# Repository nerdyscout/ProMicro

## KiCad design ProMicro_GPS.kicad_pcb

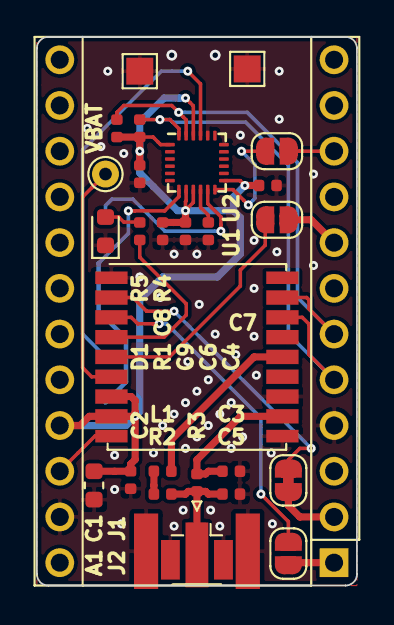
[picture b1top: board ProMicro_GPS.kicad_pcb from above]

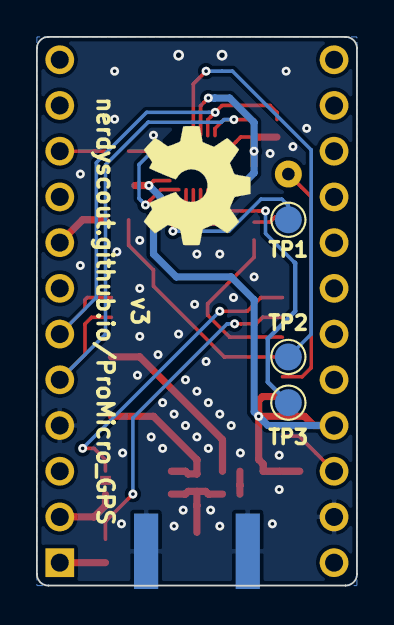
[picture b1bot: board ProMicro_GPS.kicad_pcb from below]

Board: 2 copper layers, 17.8 x 30.5 mm, 32 parts (4 on the bottom side), 24 nets.

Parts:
A1: Sparkfun_Pro_Micro_3V3; Sparkfun_Pro_Micro
C1: 4,7µ; C_0603_1608Metric
C2, C4, C7, C8, C9: 100n; C_0402_1005Metric
C3, C5: DNP; C_0402_1005Metric
C6: 10n; C_0402_1005Metric
D1: LED; LED_0603_1608Metric
J1: uFL; U.FL_Hirose_U.FL-R-SMT-1_Vertical
J2: Coax; SMA_Samtec_SMA-J-P-H-ST-EM1_EdgeMount
JP1: Jumper_NC_Small; SolderJumper-2_P1.3mm_Bridged_RoundedPad1.0x1.5mm
JP2: Jumper_NO_Small; SolderJumper-2_P1.3mm_Open_RoundedPad1.0x1.5mm
JP3, JP4: SolderJumper_2_Open; SolderJumper-2_P1.3mm_Open_RoundedPad1.0x1.5mm
L1: 27n; L_0402_1005Metric
LOGO1: Logo_Open_Hardware_Small; OSHW-Symbol_6.7x6mm_SilkScreen
R1: 1k; R_0402_1005Metric
R2: 10; R_0402_1005Metric
R3: 0; R_0402_1005Metric
R4, R5: 4k7; R_0402_1005Metric
TP1: FSYNC; TestPoint_Pad_D1.5mm
TP2: AUX_SDA; TestPoint_Pad_D1.5mm
TP3: AUX_SCL; TestPoint_Pad_D1.5mm
TP4, TP5: TestPoint; TestPoint_Pad_1.5x1.5mm
TP6: VBAT; TestPoint_THTPad_D1.5mm_Drill0.7mm
U1: SIM28ML; ublox_MAX
U2: MPU-9250; InvenSense_QFN-24_3x3mm_P0.4mm

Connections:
+3V3: A1.21, C1.1, C2.1, C6.1, C7.1, C8.1, C9.1, R4.1, R5.1, U1.7, U1.8, U2.1, U2.8, U2.9, U2.13, U2.22
D0: A1.2, JP1.2
D1: A1.1, JP2.2
D2: A1.5, R4.2, U1.16, U2.24
D3: A1.6, R5.2, U1.17, U2.23
D5: A1.8, JP3.1
D7: A1.10, JP4.2
GND: A1.4, A1.23, C1.2, C2.2, C3.2, C4.2, C5.2, C6.2, C7.2, C8.2, C9.2, D1.1, J1.2, J2.2, TP4.1, TP5.1, U1.1, U1.10, U1.12, U2.18, U2.20
unnamed: C3.1, R3.2, U1.11
unnamed: C4.1, U2.10
unnamed: C5.1, J1.1, J2.1, L1.2, R3.1
unnamed: D1.2, R1.1
unnamed: JP1.1, U1.2
unnamed: JP2.1, U1.3
unnamed: JP3.2, U1.5
unnamed: JP4.1, U2.12
unnamed: L1.1, R2.1
unnamed: R1.2, U1.4
unnamed: R2.2, U1.14
unnamed: TP1.1, U2.11
unnamed: TP2.1, U2.21
unnamed: TP3.1, U2.7
unnamed: TP6.1, U1.6
Reset: A1.22, U1.9

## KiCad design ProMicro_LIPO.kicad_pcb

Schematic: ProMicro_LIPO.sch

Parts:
A1: Sparkfun_Pro_Micro_3V3; Sparkfun_Pro_Micro
C1, C4: 10µ; C_0603_1608Metric; LCSC# C19702
C2, C5: 100n; C_0603_1608Metric; LCSC# C14663
C3, C7: 4.7µ; C_0603_1608Metric; LCSC# C19666
C6: 1µ; C_0603_1608Metric; LCSC# C15849
D1: D; D_0603_1608Metric
F1: 500mA; Fuse_0603_1608Metric; LCSC# C135323
J1: JST; JST_PH_S2B-PH-SM4-TB_1x02-1MP_P2.00mm_Horizontal
JP2: SolderJumper_3_Open; SolderJumper-3_P1.3mm_Open_RoundedPad1.0x1.5mm
L1: 6.8µ/2A; L_Bourns_SRN6045TA; LCSC# C354631
LOGO1: Logo_Open_Hardware_Small; OSHW-Symbol_6.7x6mm_SilkScreen
R1, R2, R6: 390k; R_0603_1608Metric; LCSC# C23150
R3: 2k; R_0603_1608Metric; LCSC# C22975
R4, R8: 200k; R_0603_1608Metric; LCSC# C25811
R5: 2.4M; R_0603_1608Metric; LCSC# C367738
R7: 1.1M; R_0603_1608Metric; LCSC# C169875
TP1: VBAT; TestPoint_THTPad_D2.0mm_Drill1.0mm
U1: MCP73831-2-OT; SOT-23-5; LCSC# C14879
U2: TPS61090; Texas_S-PVQFN-N16_EP2.7x2.7mm_ThermalVias; LCSC# C206167

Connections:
+3V3: A1.21 (3V3), C6.1, C7.1, R7.1, U2.1, U2.15, U2.16
D4: A1.7 (D4), JP2.2
EN: R4.1, U2.11
GND: A1.4 (GND), A1.23 (GND), C1.2, C2.1, C3.1, C4.1, C5.2, C6.2, C7.2, J1.2, R2.2, R3.1, R6.2, R8.2, U1.2, U2.5, U2.6, U2.7, U2.10, U2.13, U2.17
LDO: JP2.3, U2.12
unnamed: D1.2, F1.2
unnamed: JP2.1, R1.2, R2.1
unnamed: L1.2, U2.3, U2.4
unnamed: R3.2, U1.5
unnamed: R5.2, R6.1, U2.9
unnamed: R7.2, R8.1, U2.14
VBAT: C3.2, C4.2, C5.1, J1.1, L1.1, R1.1, R4.2, R5.1, TP1.1, U1.3, U2.8
VBUS: A1.24 (RAW), F1.1
VIN: C1.1, C2.2, D1.1, U1.4

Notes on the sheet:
VBAT/2
R3 Icharge 2k 500mA (default) 1k 1000mA
LBI/LBO Threshold Voltage
R5 = R6 * ((VBat/500mV) -1)
VBat 3.6 3.7 3.8 3.75
Output Voltage
R7 = R8 * ((Vout/Vfb) -1)
Vout 5 3,3
R5 2.4M 2.5M 2.6M 1.3M
R6 390k (default) 390k 390k 200k
R8 200k 200k
R7 1.85M 1.1M (default)
Do only populate if you want to read analog battery voltage
RxD
TxD
SDA
SCL
CLK
MISO
MOSI
CS0
INT0
TDI
TDO
TMS
TCK
close 1-2 read analog voltage close 2-3 read LBO status open 1 2 3 if no battery status required

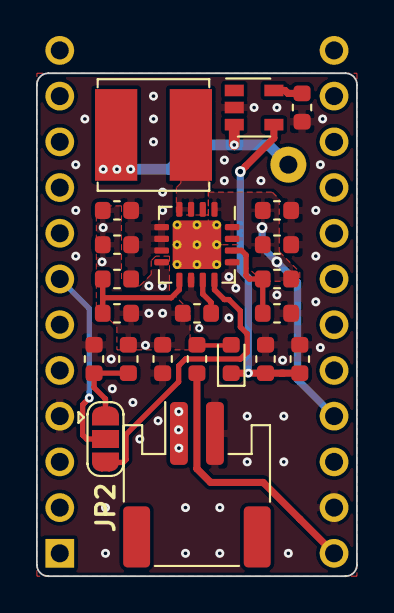
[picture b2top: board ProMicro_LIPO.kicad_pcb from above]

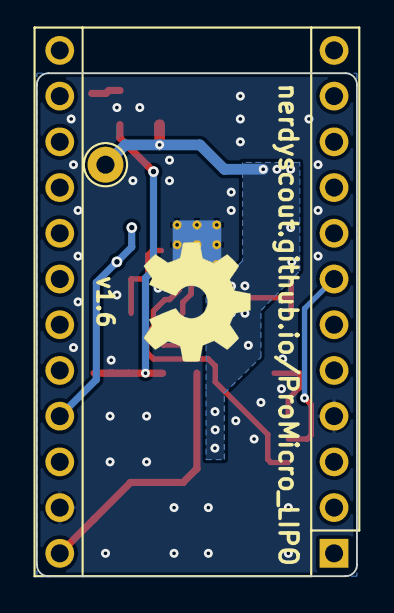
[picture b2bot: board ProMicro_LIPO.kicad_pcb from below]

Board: 2 copper layers, 17.8 x 27.9 mm, 25 parts (3 on the bottom side), 14 nets.

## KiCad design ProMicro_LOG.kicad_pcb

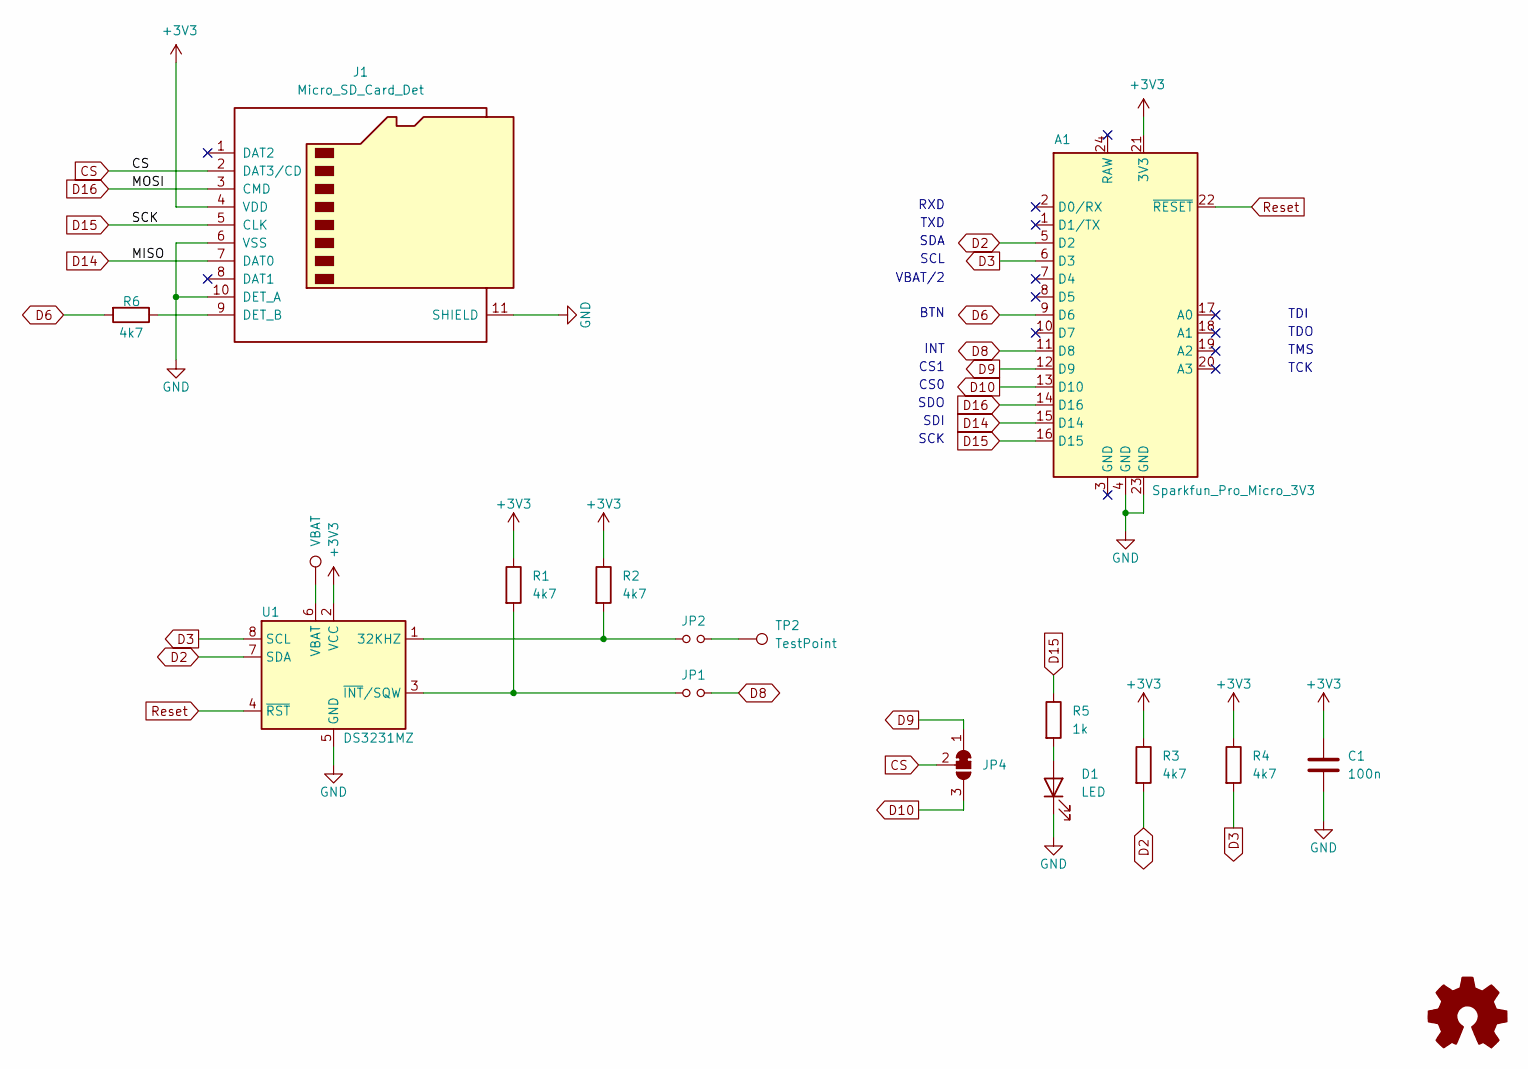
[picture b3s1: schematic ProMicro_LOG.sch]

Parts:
A1: Sparkfun_Pro_Micro_3V3; Sparkfun_Pro_Micro
C1: 100n; C_0603_1608Metric
D1: LED; LED_0603_1608Metric
J1: Micro_SD_Card_Det; microSD_HC_Molex_104031-0811
JP1, JP2: Jumper_NO_Small; SolderJumper-2_P1.3mm_Open_RoundedPad1.0x1.5mm
JP4: SolderJumper_3_Bridged12; SolderJumper-3_P1.3mm_Bridged12_RoundedPad1.0x1.5mm_NumberL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
LOGO1: Logo_Open_Hardware_Small; OSHW-Symbol_6.7x6mm_SilkScreen
R1, R2, R3, R4, R6: 4k7; R_0603_1608Metric
R5: 1k; R_0603_1608Metric
TP1: VBAT; TestPoint_THTPad_D2.0mm_Drill1.0mm
TP2: TestPoint
U1: DS3231MZ; SOIC-8_3.9x4.9mm_P1.27mm

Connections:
+3V3: A1.21 (3V3), C1.1, J1.4 (VDD), R1.1, R2.1, R3.1, R4.1, U1.2 (VCC)
CS: J1.2 (DAT3/CD), JP4.2 (C)
D2: A1.5 (D2), R3.2, U1.7 (SDA)
D3: A1.6 (D3), R4.2, U1.8 (SCL)
D6: A1.9 (D6), R6.2
D8: A1.11 (D8), JP1.2
D9: A1.12 (D9), JP4.1 (A)
D10: A1.13 (D10), JP4.3 (B)
D14: A1.15 (D14), J1.7 (DAT0)
D15: A1.16 (D15), J1.5 (CLK), R5.1
D16: A1.14 (D16), J1.3 (CMD)
GND: A1.4 (GND), A1.23 (GND), C1.2, D1.1 (K), J1.6 (VSS), J1.10 (DET_A), J1.11 (SHIELD), U1.5 (GND)
unnamed: D1.2 (A), R5.2
unnamed: J1.9 (DET_B), R6.1
unnamed: JP1.1, R1.2, U1.3 (~INT~/SQW)
unnamed: JP2.1, R2.2, U1.1 (32KHZ)
unnamed: TP1.1, U1.6 (VBAT)
unnamed: JP2.2, TP2.1
Reset: A1.22 (~RESET), U1.4 (~RST)

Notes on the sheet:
VBAT/2
CS1
CS0
TDI
TDO
TMS
TCK
RXD
TXD
SDA
SCL
SDO
SDI
SCK
BTN
INT

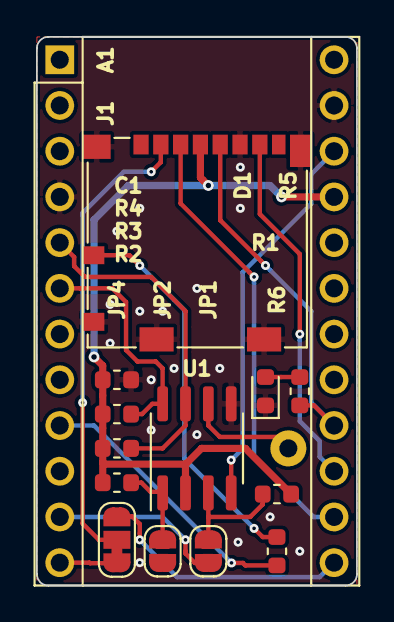
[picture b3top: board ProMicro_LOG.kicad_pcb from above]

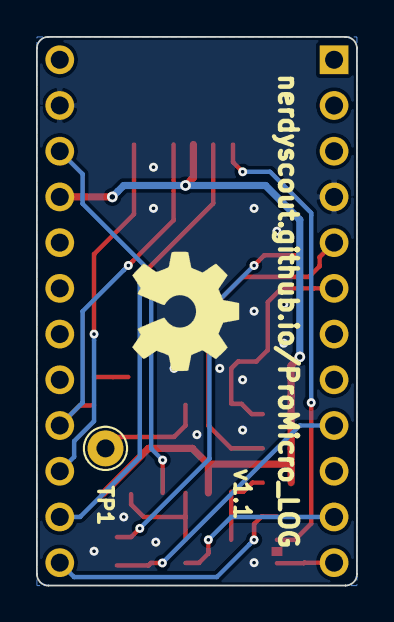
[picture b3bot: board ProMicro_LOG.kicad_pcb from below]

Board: 2 copper layers, 17.8 x 30.5 mm, 16 parts (2 on the bottom side), 18 nets.

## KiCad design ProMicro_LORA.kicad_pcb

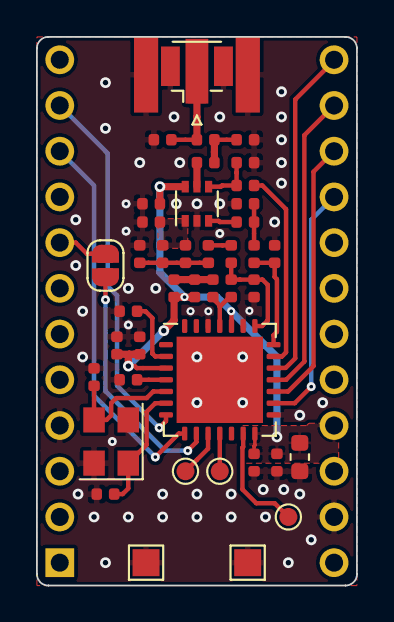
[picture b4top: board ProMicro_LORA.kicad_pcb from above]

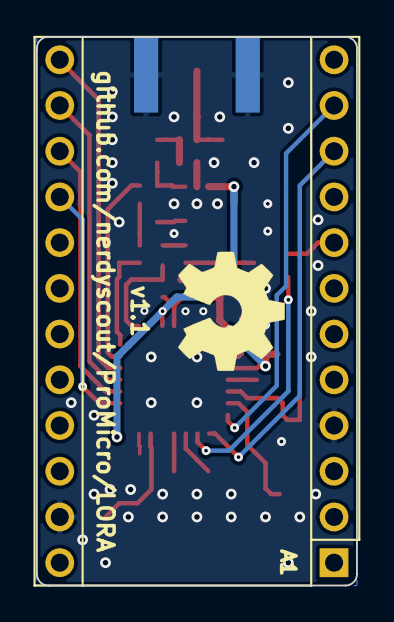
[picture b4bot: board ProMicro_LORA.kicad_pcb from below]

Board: 2 copper layers, 17.8 x 30.5 mm, 44 parts (2 on the bottom side), 30 nets.

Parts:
A1: Sparkfun_Pro_Micro_3V3; Sparkfun_Pro_Micro
C1, C4: 15p; C_0402_1005Metric
C2: 1.5pF; C_0402_1005Metric
C3: 33pF; C_0402_1005Metric
C5: 4.7pF; C_0402_1005Metric
C6: 3.3pF; C_0402_1005Metric
C7: 47pF; C_0402_1005Metric
C8: 1.8pF; C_0402_1005Metric
C9, C15, C18: 47p; C_0402_1005Metric
C10, C11, C24: DNP; C_0402_1005Metric
C12: 1.2pF; C_0402_1005Metric
C13, C14: 1nF; C_0402_1005Metric
C16, C17, C19, C20, C21: 100n; C_0402_1005Metric
C22: 1µ; C_0402_1005Metric
C23: 10µ; C_0603_1608Metric
C25: F; C_0402_1005Metric
J1: SMA; U.FL_Hirose_U.FL-R-SMT-1_Vertical
J2: COAX; SMA_Samtec_SMA-J-P-H-ST-EM1_EdgeMount
JP1: SolderJumper_2_Open; SolderJumper-2_P1.3mm_Open_RoundedPad1.0x1.5mm
L1: 33nH; L_0402_1005Metric
L2, L3: 10nH; L_0402_1005Metric
L4: 6.2nH; L_0402_1005Metric
L5: 0R; L_0402_1005Metric
LOGO1: Logo_Open_Hardware_Small; OSHW-Symbol_6.7x6mm_SilkScreen
R1: 1k; R_0402_1005Metric
TP2: DIO2; TestPoint_Pad_D1.0mm
TP3: DIO3; TestPoint_Pad_D1.0mm
TP4: DIO5; TestPoint_Pad_D1.0mm
TP5, TP6: TestPoint; TestPoint_Pad_1.5x1.5mm
U1: SX1276; QFN-28-1EP_6x6mm_P0.65mm_EP4.8x4.8mm
U2: AS179-92LF; SOT-363_SC-70-6
Y1: 32Mhz; Crystal_SMD_SeikoEpson_FA238V-4Pin_3.2x2.5mm

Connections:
+3V3: A1.21, C14.1, C15.1, C16.2, C17.2, C18.1, C19.2, C22.1, C23.1, U1.3, U1.14, U1.24, U2.6
D5: A1.8, JP1.2
D7: A1.10, U1.8
D8: A1.11, U1.7
D10: A1.13, U1.19
GND: A1.4, A1.23, C1.2, C2.1, C4.2, C5.2, C6.2, C8.2, C10.2, C11.2, C13.2, C14.2, C15.2, C16.1, C17.1, C18.2, C19.1, C20.2, C21.2, C22.2, C23.2, C24.2, C25.2, J1.2, J2.2, TP5.1, TP6.1, U1.15, U1.23, U1.26, U1.29, U2.2, Y1.2, Y1.4
MISO: A1.15, U1.17
MOSI: A1.14, U1.18
unnamed: C1.1, U1.6, Y1.1
unnamed: C3.1, L2.1
unnamed: C4.1, U1.5, Y1.3
unnamed: C6.1, C7.2, L3.2
unnamed: C7.1, U2.3
unnamed: C9.2, U2.5
unnamed: C9.1, C10.1, L5.1
unnamed: C11.1, J1.1, J2.1, L5.2
unnamed: C8.1, C12.1, L4.2, U2.1
unnamed: C5.1, C12.2, L2.2, L4.1
unnamed: C13.1, R1.2, U2.4
unnamed: C20.1, U1.4
unnamed: C21.1, U1.2
unnamed: JP1.1, U1.9
unnamed: R1.1, U1.20
unnamed: TP2.1, U1.10
unnamed: TP3.1, U1.11
unnamed: TP4.1, U1.13
RFI-HF: C24.1, L3.1, U1.21
RFO_HF: C2.2, C3.2, L1.2, U1.22
SCK: A1.16, U1.16
VR_PA: C25.1, L1.1, U1.25

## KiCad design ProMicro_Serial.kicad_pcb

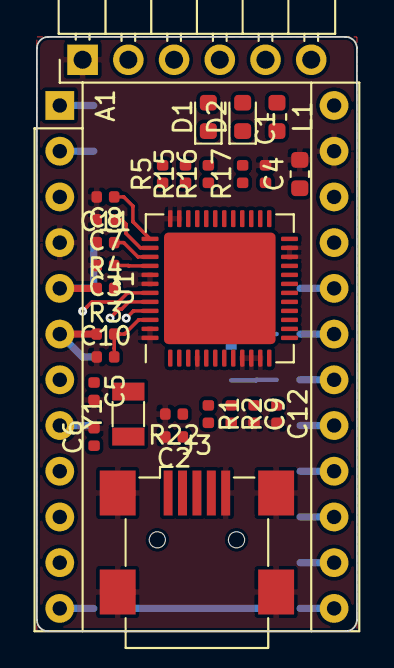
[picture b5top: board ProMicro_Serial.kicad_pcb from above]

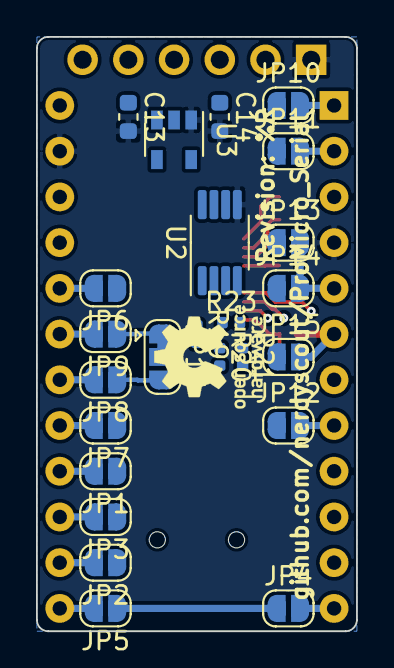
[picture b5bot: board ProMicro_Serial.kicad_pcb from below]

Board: 2 copper layers, 17.8 x 33.0 mm, 54 parts (25 on the bottom side), 44 nets.

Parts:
A1: Sparkfun_Pro_Micro_3V3; Sparkfun_Pro_Micro
C1, C3, C7, C8, C10, C11, C12: 100n; C_0402_1005Metric
C2, C9: 4.7µ; C_0402_1005Metric
C4: 10µ; C_0603_1608Metric
C5, C6: 27p; C_0402_1005Metric
C13: 1µ; C_0603_1608Metric
C14: 100n; C_0603_1608Metric
D1: TX; LED_0603_1608Metric
D2: RX; LED_0603_1608Metric
J2: Conn_01x06; PinHeader_1x06_P2.54mm_Horizontal
J3: USB_B_Mini; USB_Mini-B_Wuerth_65100516121_Horizontal
JP1, JP2, JP3, JP4, JP5, JP6, JP7, JP8, JP9, JP10, JP11, JP12, JP13, JP14, JP15: Jumper_NO_Small; SolderJumper-2_P1.3mm_Open_RoundedPad1.0x1.5mm
JP16: Jumper_3_Bridged12; SolderJumper-3_P1.3mm_Bridged12_RoundedPad1.0x1.5mm
L1: 0; L_0603_1608Metric
LOGO1: Logo_Open_Hardware_Small; OSHW-Logo_5.7x6mm_SilkScreen
R1, R2: 22; R_0402_1005Metric
R3, R4: 4k7; R_0402_1005Metric
R5: 1k; R_0402_1005Metric
R15: 39k; R_0402_1005Metric
R16, R17: 220; R_0402_1005Metric
R19, R20, R21: 10k; R_0402_1005Metric
R22: 12k; R_0402_1005Metric
R23: 2k; R_0402_1005Metric
U1: FT232H; QFN-48-1EP_8x8mm_P0.5mm_EP6.2x6.2mm
U2: 93CxxB; MSOP-8_3x3mm_P0.65mm
U3: AZ1117-3.3; SOT-23-5
Y1: 12Mhz; Crystal_SMD_3215-2Pin_3.2x1.5mm

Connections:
+3V3: A1.21, C1.1, C4.1, C9.1, C10.2, C11.2, C12.1, C14.1, D1.2, D2.2, J2.3, R3.2, R4.2, R5.2, R19.2, R20.2, R21.2, U1.3, U1.8, U1.12, U1.24, U1.39, U1.46, U2.8, U3.2
+5V: A1.24, C13.1, L1.1, R15.2, U3.3
/EECLK: R20.1, U1.44, U2.2
/EECS: R19.1, U1.45, U2.1
/EEDAT: R23.1, U1.43, U2.3
A0: A1.17, JP7.2
A1: A1.18, JP8.2
A2: A1.19, JP9.2
A3: A1.20, JP6.2
ACBUS0: A1.22, JP12.1, U1.21
ADBUS0: J2.4, JP1.1, JP6.1, JP10.1, JP15.1, U1.13
ADBUS1: J2.5, JP2.1, JP7.1, JP11.1, JP13.1, U1.14
ADBUS2: JP3.1, JP8.1, JP14.1, JP16.3, U1.15
ADBUS3: JP4.1, JP5.1, JP9.1, JP16.1, U1.16
ADBUS4: J2.6, U1.17
D0: A1.2, JP11.2
D1: A1.1, JP10.2
D2: A1.5, JP13.2, JP14.2, R4.1
D3: A1.6, JP15.2, R3.1
D5: A1.8, JP12.2
D9: A1.12, JP4.2
D10: A1.13, JP5.2
D14: A1.15, JP3.2
D15: A1.16, JP1.2
D16: A1.14, JP2.2
GND: A1.4, A1.23, C1.2, C2.2, C3.2, C4.2, C5.2, C6.2, C7.2, C8.2, C9.2, C10.1, C11.1, C12.2, C13.2, C14.2, J2.1, J3.5, J3.6, R22.2, U1.4, U1.9, U1.10, U1.11, U1.22, U1.23, U1.35, U1.36, U1.41, U1.42, U1.47, U1.48, U2.5, U3.1
unnamed: C2.1, C3.1, J3.1, L1.2, U1.40
unnamed: C5.1, U1.1, Y1.1
unnamed: C6.1, U1.2, Y1.2
unnamed: C7.1, U1.38
unnamed: C8.1, U1.37
unnamed: D1.1, R16.2
unnamed: D2.1, R17.2
unnamed: J2.2, JP16.2
unnamed: J3.2, R1.2
unnamed: J3.3, R2.2
unnamed: R1.1, U1.6
unnamed: R2.1, U1.7
unnamed: R5.1, U1.34
unnamed: R21.1, R23.2, U2.4
unnamed: R22.1, U1.5
PWRSAV: R15.1, U1.31
RXLED: R17.1, U1.27
TXLED: R16.1, U1.28

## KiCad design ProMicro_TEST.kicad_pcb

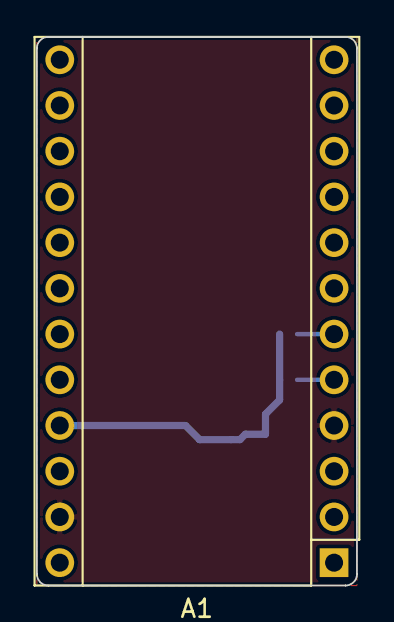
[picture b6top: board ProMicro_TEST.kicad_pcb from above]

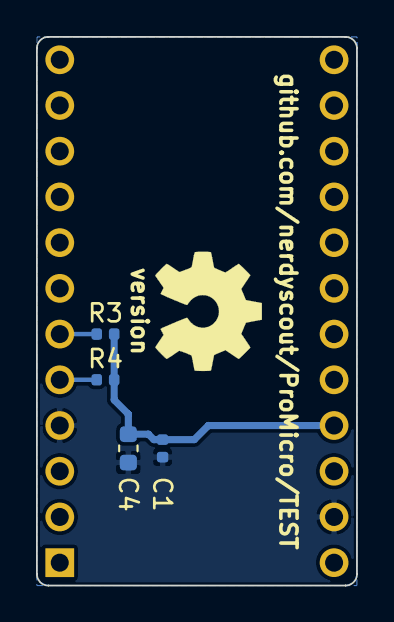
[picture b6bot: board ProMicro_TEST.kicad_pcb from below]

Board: 2 copper layers, 17.8 x 30.5 mm, 6 parts (5 on the bottom side), 4 nets.

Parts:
A1: Sparkfun_Pro_Micro_3V3; Sparkfun_Pro_Micro
C1: 100n; C_0402_1005Metric
C4: 10µ; C_0603_1608Metric
LOGO1: Logo_Open_Hardware_Small; OSHW-Symbol_6.7x6mm_SilkScreen
R3, R4: 4k7; R_0402_1005Metric

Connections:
+3V3: A1.21, C1.1, C4.1, R3.2, R4.2
GND: A1.4, A1.23, C1.2, C4.2
SCL: A1.6, R3.1
SDA: A1.5, R4.1

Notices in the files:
ProMicro_GPS.kicad_pcb:
CERN Open Hardware Licence v1.2
